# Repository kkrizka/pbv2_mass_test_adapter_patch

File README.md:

A simple adapter to connect the output pins of the [pbv2_mass_test_adapter](https://github.com/kkrizka/pbv2_mass_test_adapter) to helpful cables.

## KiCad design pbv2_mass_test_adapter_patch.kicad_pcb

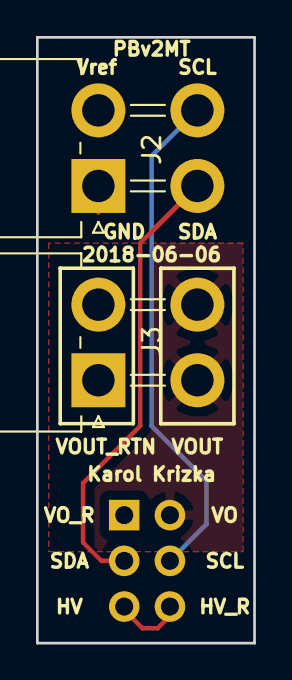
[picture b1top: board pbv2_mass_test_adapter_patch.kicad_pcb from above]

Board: 2 copper layers, 12.1 x 33.7 mm, 3 parts (1 on the bottom side), 5 nets.

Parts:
J1: Conn_02x03_Odd_Even; Socket_Strip_Straight_2x03_Pitch2.54mm
J2, J3: Conn_02x02_Counter_Clockwise; Molex_MiniFit-JR-5569-04A2_2x02x4.20mm_Angled

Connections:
/HVOUT: J1.5, J1.6
/SCL: J1.4, J2.4
/SDA: J1.3, J2.3
/VOUT: J1.2, J3.3, J3.4
GND: J1.1, J2.1, J3.1, J3.2

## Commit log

2018-06-07 Initial import.
2018-06-07 Add README.
2018-06-07 Add .gitignore
